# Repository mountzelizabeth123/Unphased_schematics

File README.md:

# UnPhased KiCad Project Repository

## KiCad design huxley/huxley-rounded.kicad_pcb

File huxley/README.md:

Board: Huxley
# Layers: 4
Board Dimensions: 4.88in x 4.88in (124mm x 124mm)
Min Size Hole: 0.01in
# Holes: 528
Assembly Both Sides: Y
Standard Chip IO: N
Blink Vias: N
Via in pads: Y

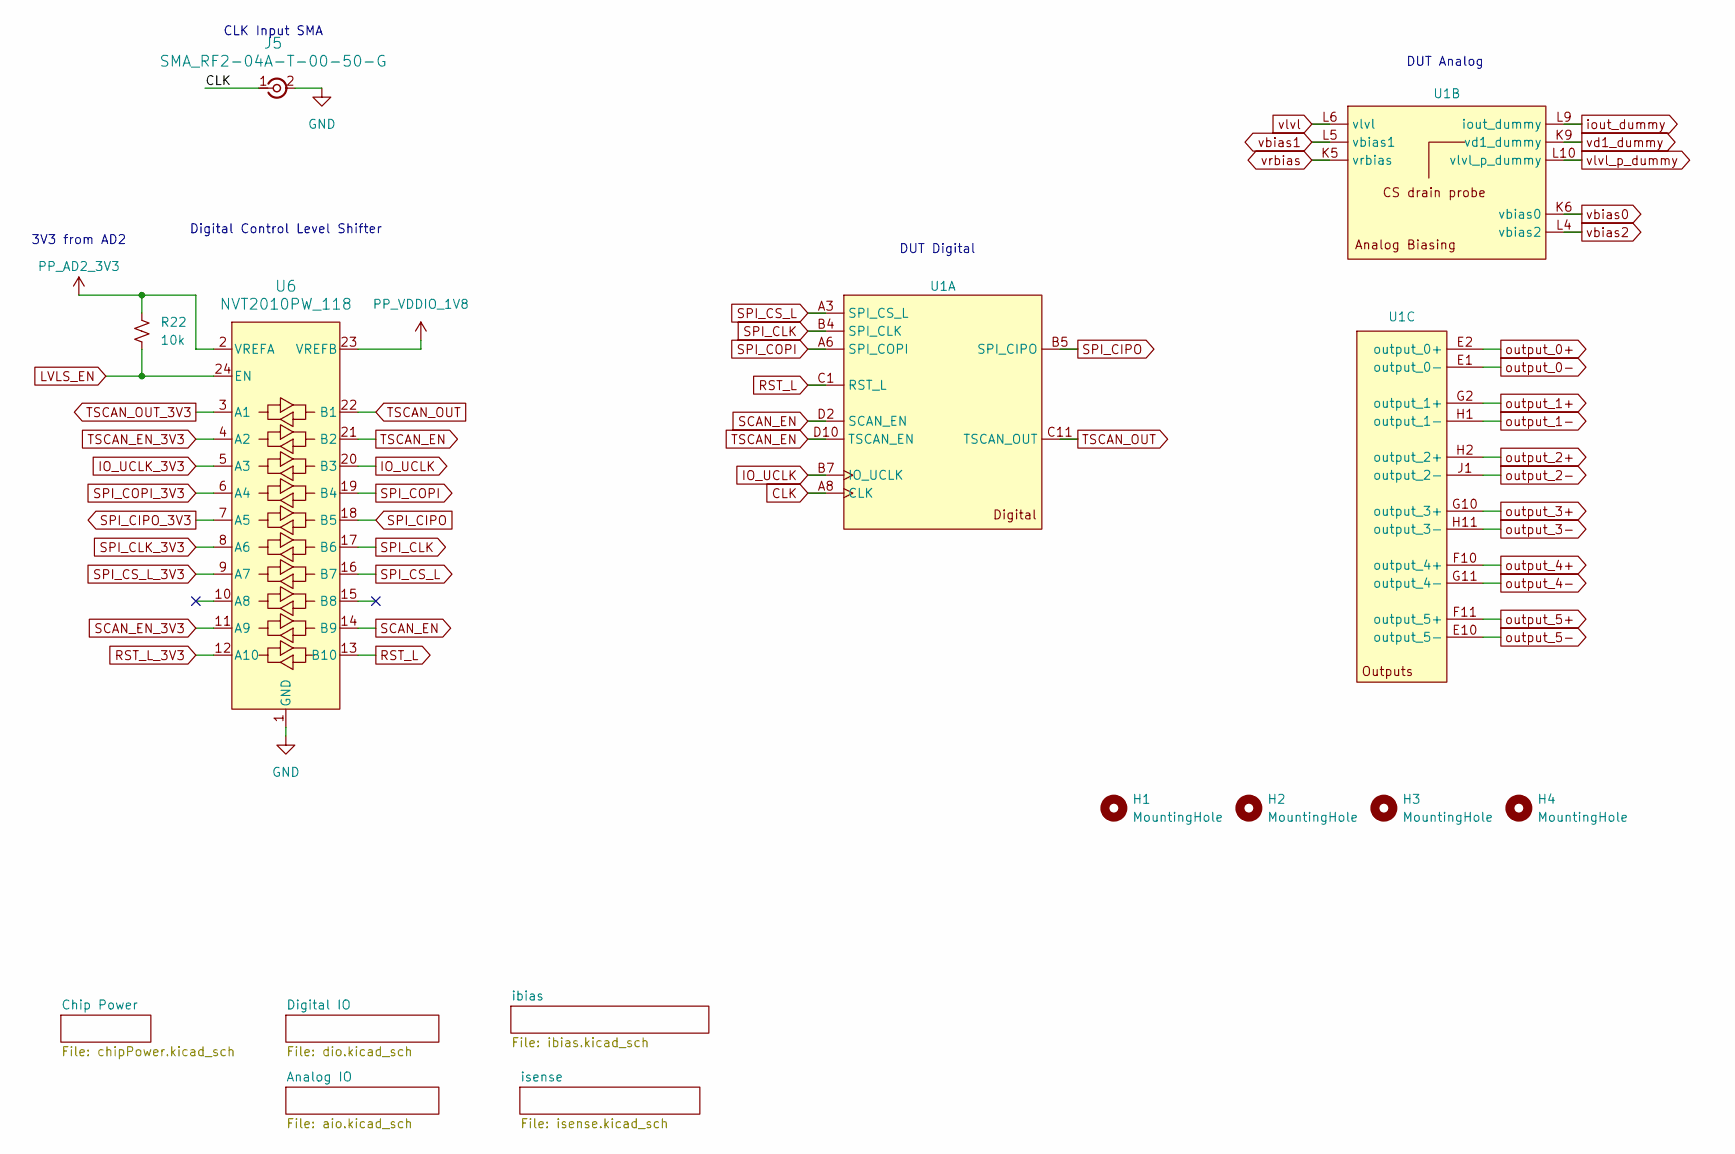
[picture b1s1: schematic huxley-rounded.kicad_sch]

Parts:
H1, H2, H3, H4: MountingHole; MountingHole_3.2mm_M3_DIN965_Pad_TopBottom
J5: SMA_RF2-04A-T-00-50-G; CONN_RF2-04A-T-00-50-G_ADM
R22: 10k; R_0603_1608Metric
U1: CPG08462_Full
U6: NVT2010PW_118; TSSOP24_SOT355-1_NXP

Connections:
CLK: J5.1, U1.A8 (CLK); also elsewhere on the board
GND: J5.2, J5.3 (Ext), J5.4 (Ext), J5.5 (Ext), U6.1 (GND); also elsewhere on the board
IO_UCLK: U1.B7 (IO_UCLK), U6.20 (B3)
IO_UCLK_3V3: U6.5 (A3); also elsewhere on the board
LVLS_EN: R22.2, U6.24 (EN); also elsewhere on the board
PP_AD2_3V3: R22.1, U6.2 (VREFA); also elsewhere on the board
PP_VDDIO_1V8: U6.23 (VREFB); also elsewhere on the board
RST_L: U1.C1 (RST_L), U6.13 (B10)
RST_L_3V3: U6.12 (A10); also elsewhere on the board
SCAN_EN: U1.D2 (SCAN_EN), U6.14 (B9)
SCAN_EN_3V3: U6.11 (A9); also elsewhere on the board
SPI_CIPO: U1.B5 (SPI_CIPO), U6.18 (B5)
SPI_CIPO_3V3: U6.7 (A5); also elsewhere on the board
SPI_CLK: U1.B4 (SPI_CLK), U6.17 (B6)
SPI_CLK_3V3: U6.8 (A6); also elsewhere on the board
SPI_COPI: U1.A6 (SPI_COPI), U6.19 (B4)
SPI_COPI_3V3: U6.6 (A4); also elsewhere on the board
SPI_CS_L: U1.A3 (SPI_CS_L), U6.16 (B7)
SPI_CS_L_3V3: U6.9 (A7); also elsewhere on the board
TSCAN_EN: U1.D10 (TSCAN_EN), U6.21 (B2)
TSCAN_EN_3V3: U6.4 (A2); also elsewhere on the board
TSCAN_OUT: U1.C11 (TSCAN_OUT), U6.22 (B1)
TSCAN_OUT_3V3: U6.3 (A1); also elsewhere on the board
iout_dummy: U1.L9 (iout_dummy); also elsewhere on the board
output_0+: U1.E2 (output_0+); also elsewhere on the board
output_0-: U1.E1 (output_0-); also elsewhere on the board
output_1+: U1.G2 (output_1+); also elsewhere on the board
output_1-: U1.H1 (output_1-); also elsewhere on the board
output_2+: U1.H2 (output_2+); also elsewhere on the board
output_2-: U1.J1 (output_2-); also elsewhere on the board
output_3+: U1.G10 (output_3+); also elsewhere on the board
output_3-: U1.H11 (output_3-); also elsewhere on the board
output_4+: U1.F10 (output_4+); also elsewhere on the board
output_4-: U1.G11 (output_4-); also elsewhere on the board
output_5+: U1.F11 (output_5+); also elsewhere on the board
output_5-: U1.E10 (output_5-); also elsewhere on the board
vbias0: U1.K6 (vbias0); also elsewhere on the board
vbias1: U1.L5 (vbias1); also elsewhere on the board
vbias2: U1.L4 (vbias2); also elsewhere on the board
vd1_dummy: U1.K9 (vd1_dummy); also elsewhere on the board
vlvl: U1.L6 (vlvl); also elsewhere on the board
vlvl_p_dummy: U1.L10 (vlvl_p_dummy); also elsewhere on the board
vrbias: U1.K5 (vrbias); also elsewhere on the board

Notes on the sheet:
DUT Digital
DUT Analog
CLK Input SMA
3V3 from AD2
Digital Control Level Shifter

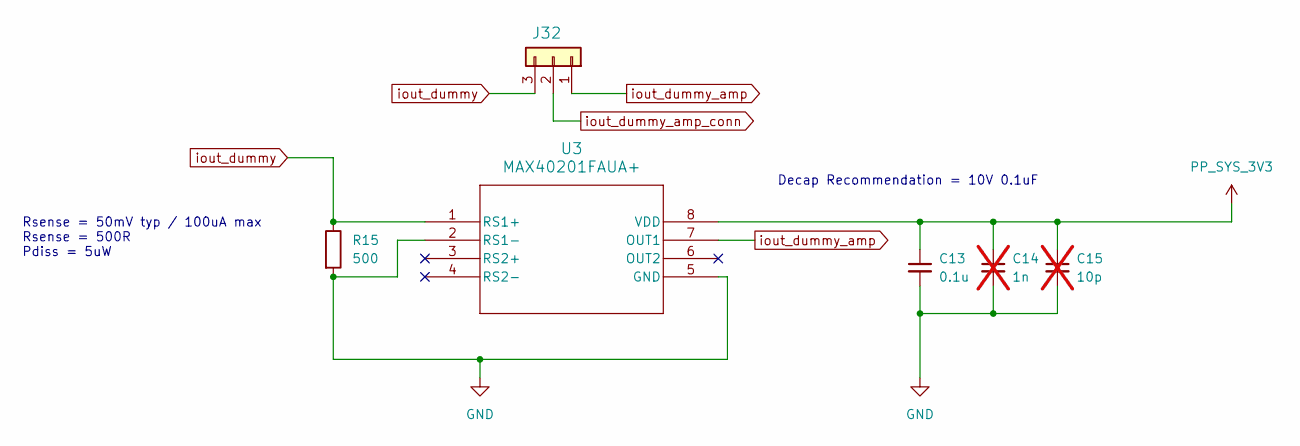
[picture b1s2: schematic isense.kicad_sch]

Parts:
C13: 0.1u; C_0603_1608Metric
C14: 1n; C_0603_1608Metric; not fitted
C15: 10p; C_0603_1608Metric; not fitted
J32: 61300211121; PinHeader_1x03_P2.54mm_Vertical
R15: 500; R_0603_1608Metric
U3: MAX40201FAUA+

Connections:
GND: C13.2, C14.2, C15.2, R15.2, U3.2 (RS1-), U3.5 (GND); also elsewhere on the board
PP_SYS_3V3: C13.1, C14.1, C15.1, U3.8 (VDD); also elsewhere on the board
iout_dummy: J32.3, R15.1, U3.1 (RS1+); also elsewhere on the board
iout_dummy_amp: J32.1, U3.7 (OUT1)
iout_dummy_amp_conn: J32.2; also elsewhere on the board

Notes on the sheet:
Decap Recommendation = 10V 0.1uF
Rsense = 50mV typ / 100uA max Rsense = 500R Pdiss = 5uW

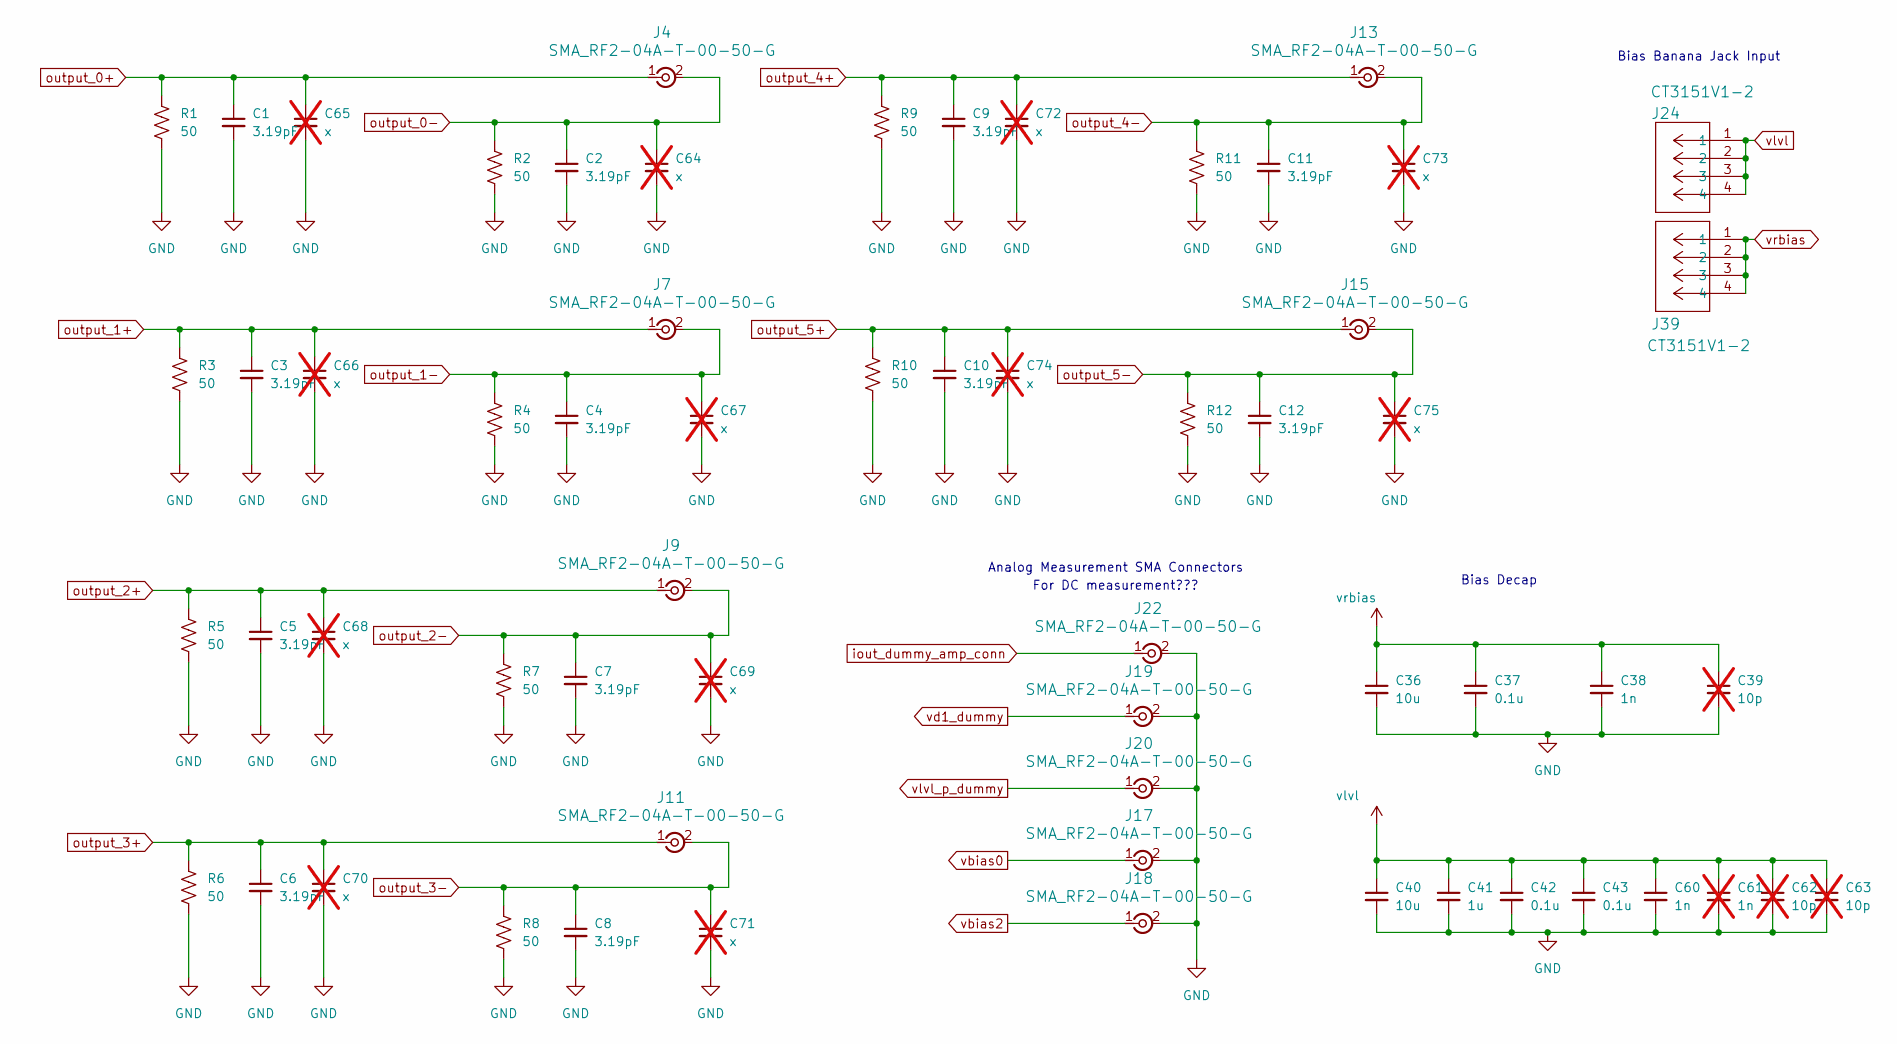
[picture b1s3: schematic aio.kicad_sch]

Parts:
C1, C2, C3, C4, C5, C6, C7, C8, C9, C10, C11, C12: 3.19pF; C_0603_1608Metric
C36, C40: 10u; C_0603_1608Metric
C37, C42, C43: 0.1u; C_0603_1608Metric
C38, C60: 1n; C_0603_1608Metric
C39, C62, C63: 10p; C_0603_1608Metric; not fitted
C41: 1u; C_0603_1608Metric
C61: 1n; C_0603_1608Metric; not fitted
C64, C65, C66, C67, C68, C69, C70, C71, C72, C73, C74, C75: x; C_0603_1608Metric; not fitted
J4, J7, J9, J11, J13, J15, J17, J18, J19, J20, J22: SMA_RF2-04A-T-00-50-G; CONN_RF2-04A-T-00-50-G_ADM
J24, J39: CT3151V1-2; banana_plug_CT3151V1-0
R1, R2, R3, R4, R5, R6, R7, R8, R9, R10, R11, R12: 50; R_0603_1608Metric_Vishay_WBT

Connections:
GND: C1.2, C2.2, C3.2, C4.2, C5.2, C6.2, C7.2, C8.2, C9.2, C10.2, C11.2, C12.2, C36.2, C37.2, C38.2, C39.2, C40.2, C41.2, C42.2, C43.2, C60.2, C61.2, C62.2, C63.2, C64.2, C65.2, C66.2, C67.2, C68.2, C69.2, C70.2, C71.2, C72.2, C73.2, C74.2, C75.2, J17.2, J17.3 (Ext), J17.4 (Ext), J17.5 (Ext), J18.2, J18.3 (Ext), J18.4 (Ext), J18.5 (Ext), J19.2, J19.3 (Ext), J19.4 (Ext), J19.5 (Ext), J20.2, J20.3 (Ext), J20.4 (Ext), J20.5 (Ext), J22.2, J22.3 (Ext), J22.4 (Ext), J22.5 (Ext), R1.2, R2.2, R3.2, R4.2, R5.2, R6.2, R7.2, R8.2, R9.2, R10.2, R11.2, R12.2; also elsewhere on the board
iout_dummy_amp_conn: J22.1; also elsewhere on the board
output_0+: C1.1, C65.1, J4.1, R1.1; also elsewhere on the board
output_0-: C2.1, C64.1, J4.2, J4.3 (Ext), J4.4 (Ext), J4.5 (Ext), R2.1; also elsewhere on the board
output_1+: C3.1, C66.1, J7.1, R3.1; also elsewhere on the board
output_1-: C4.1, C67.1, J7.2, J7.3 (Ext), J7.4 (Ext), J7.5 (Ext), R4.1; also elsewhere on the board
output_2+: C5.1, C68.1, J9.1, R5.1; also elsewhere on the board
output_2-: C7.1, C69.1, J9.2, J9.3 (Ext), J9.4 (Ext), J9.5 (Ext), R7.1; also elsewhere on the board
output_3+: C6.1, C70.1, J11.1, R6.1; also elsewhere on the board
output_3-: C8.1, C71.1, J11.2, J11.3 (Ext), J11.4 (Ext), J11.5 (Ext), R8.1; also elsewhere on the board
output_4+: C9.1, C72.1, J13.1, R9.1; also elsewhere on the board
output_4-: C11.1, C73.1, J13.2, J13.3 (Ext), J13.4 (Ext), J13.5 (Ext), R11.1; also elsewhere on the board
output_5+: C10.1, C74.1, J15.1, R10.1; also elsewhere on the board
output_5-: C12.1, C75.1, J15.2, J15.3 (Ext), J15.4 (Ext), J15.5 (Ext), R12.1; also elsewhere on the board
vbias0: J17.1; also elsewhere on the board
vbias2: J18.1; also elsewhere on the board
vd1_dummy: J19.1; also elsewhere on the board
vlvl: C40.1, C41.1, C42.1, C43.1, C60.1, C61.1, C62.1, C63.1, J24.1, J24.2, J24.3, J24.4; also elsewhere on the board
vlvl_p_dummy: J20.1; also elsewhere on the board
vrbias: C36.1, C37.1, C38.1, C39.1, J39.1, J39.2, J39.3, J39.4; also elsewhere on the board

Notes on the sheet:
Analog Measurement SMA Connectors
Bias Decap
Bias Banana Jack Input
For DC measurement???

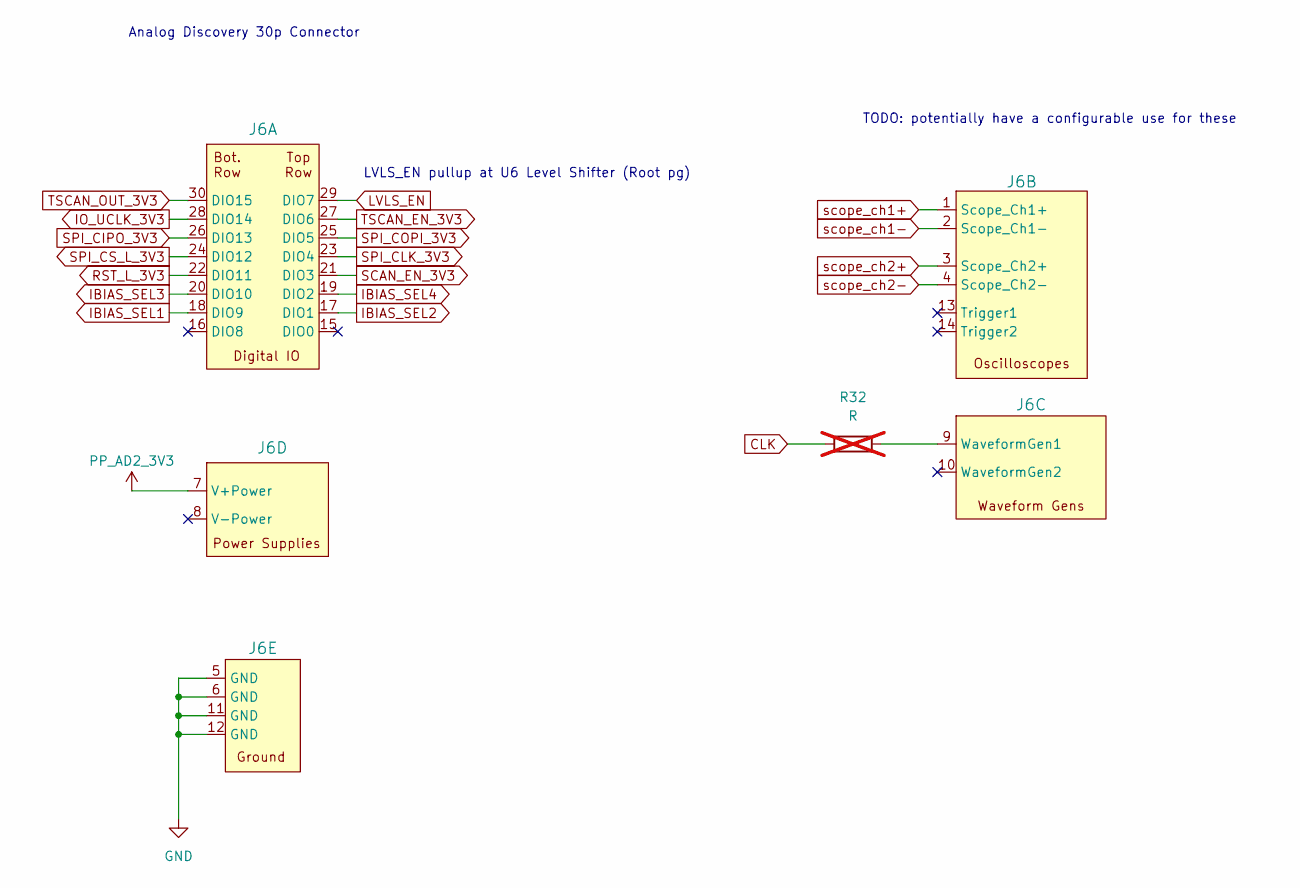
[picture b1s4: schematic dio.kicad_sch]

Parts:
J6: PinHeader_2x15_P2.54mm_Horizontal
R32: R; R_0603_1608Metric; not fitted

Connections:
CLK: R32.1; also elsewhere on the board
GND: J6.5 (GND), J6.6 (GND), J6.11 (GND), J6.12 (GND); also elsewhere on the board
IBIAS_SEL1: J6.18 (DIO9); also elsewhere on the board
IBIAS_SEL2: J6.17 (DIO1); also elsewhere on the board
IBIAS_SEL3: J6.20 (DIO10); also elsewhere on the board
IBIAS_SEL4: J6.19 (DIO2); also elsewhere on the board
IO_UCLK_3V3: J6.28 (DIO14); also elsewhere on the board
LVLS_EN: J6.29 (DIO7); also elsewhere on the board
unnamed: J6.9 (WaveformGen1), R32.2
PP_AD2_3V3: J6.7 (V+Power); also elsewhere on the board
RST_L_3V3: J6.22 (DIO11); also elsewhere on the board
SCAN_EN_3V3: J6.21 (DIO3); also elsewhere on the board
SPI_CIPO_3V3: J6.26 (DIO13); also elsewhere on the board
SPI_CLK_3V3: J6.23 (DIO4); also elsewhere on the board
SPI_COPI_3V3: J6.25 (DIO5); also elsewhere on the board
SPI_CS_L_3V3: J6.24 (DIO12); also elsewhere on the board
TSCAN_EN_3V3: J6.27 (DIO6); also elsewhere on the board
TSCAN_OUT_3V3: J6.30 (DIO15); also elsewhere on the board
scope_ch1+: J6.1 (Scope_Ch1+)
scope_ch1-: J6.2 (Scope_Ch1-)
scope_ch2+: J6.3 (Scope_Ch2+)
scope_ch2-: J6.4 (Scope_Ch2-)

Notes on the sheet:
Analog Discovery 30p Connector
LVLS_EN pullup at U6 Level Shifter (Root pg)
TODO: potentially have a configurable use for these

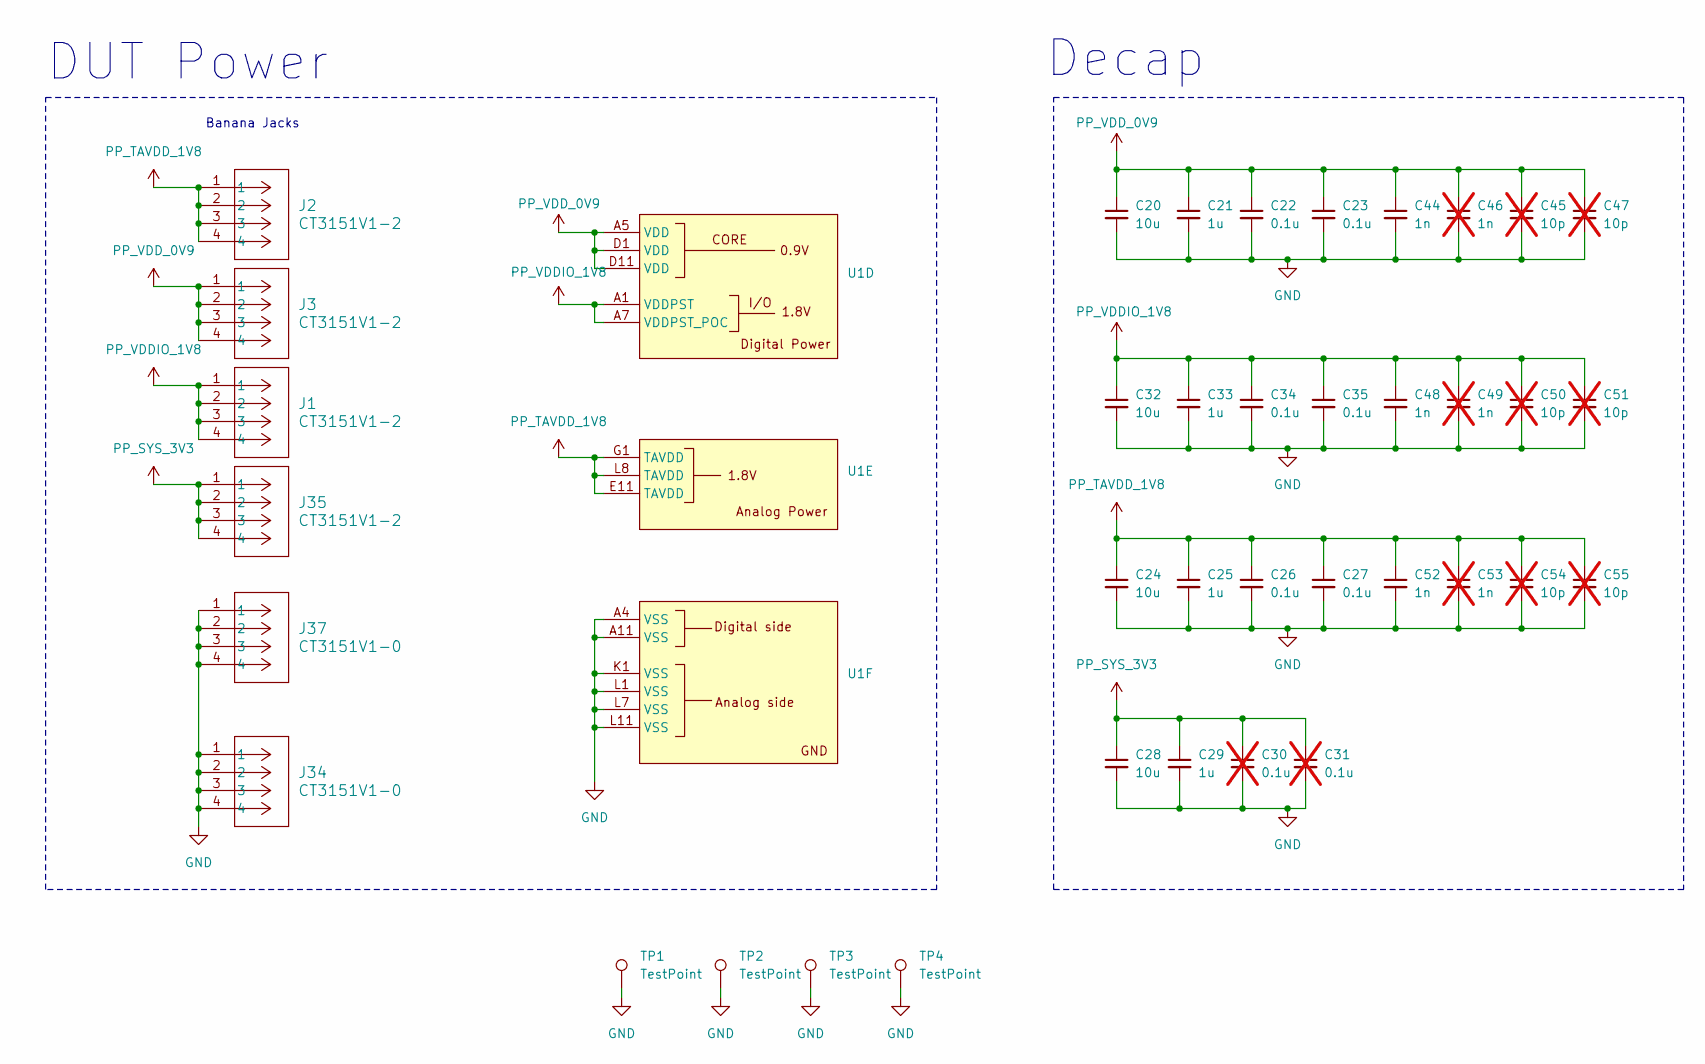
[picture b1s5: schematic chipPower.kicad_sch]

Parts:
C20, C24, C28, C32: 10u; C_0603_1608Metric
C21, C25, C29, C33: 1u; C_0603_1608Metric
C22, C23, C26, C27, C34, C35: 0.1u; C_0603_1608Metric
C30, C31: 0.1u; C_0603_1608Metric; not fitted
C44, C48, C52: 1n; C_0603_1608Metric
C45, C47, C50, C51, C54, C55: 10p; C_0603_1608Metric; not fitted
C46, C49, C53: 1n; C_0603_1608Metric; not fitted
J1, J2, J3, J35: CT3151V1-2; banana_plug_CT3151V1-0
J34, J37: CT3151V1-0; banana_plug_CT3151V1-0
TP1, TP2, TP3, TP4: TestPoint; TestPoint_Pad_D3.0mm
U1: CPG08462_Full

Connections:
GND: C20.2, C21.2, C22.2, C23.2, C24.2, C25.2, C26.2, C27.2, C28.2, C29.2, C30.2, C31.2, C32.2, C33.2, C34.2, C35.2, C44.2, C45.2, C46.2, C47.2, C48.2, C49.2, C50.2, C51.2, C52.2, C53.2, C54.2, C55.2, J34.1, J34.2, J34.3, J34.4, J37.1, J37.2, J37.3, J37.4, TP1.1, TP2.1, TP3.1, TP4.1, U1.A4 (VSS), U1.A11 (VSS), U1.K1 (VSS), U1.L1 (VSS), U1.L7 (VSS), U1.L11 (VSS); also elsewhere on the board
PP_SYS_3V3: C28.1, C29.1, C30.1, C31.1, J35.1, J35.2, J35.3, J35.4; also elsewhere on the board
PP_TAVDD_1V8: C24.1, C25.1, C26.1, C27.1, C52.1, C53.1, C54.1, C55.1, J2.1, J2.2, J2.3, J2.4, U1.E11 (TAVDD), U1.G1 (TAVDD), U1.L8 (TAVDD)
PP_VDDIO_1V8: C32.1, C33.1, C34.1, C35.1, C48.1, C49.1, C50.1, C51.1, J1.1, J1.2, J1.3, J1.4, U1.A1 (VDDPST), U1.A7 (VDDPST_POC); also elsewhere on the board
PP_VDD_0V9: C20.1, C21.1, C22.1, C23.1, C44.1, C45.1, C46.1, C47.1, J3.1, J3.2, J3.3, J3.4, U1.A5 (VDD), U1.D1 (VDD), U1.D11 (VDD)

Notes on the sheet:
Decap
DUT Power
Banana Jacks

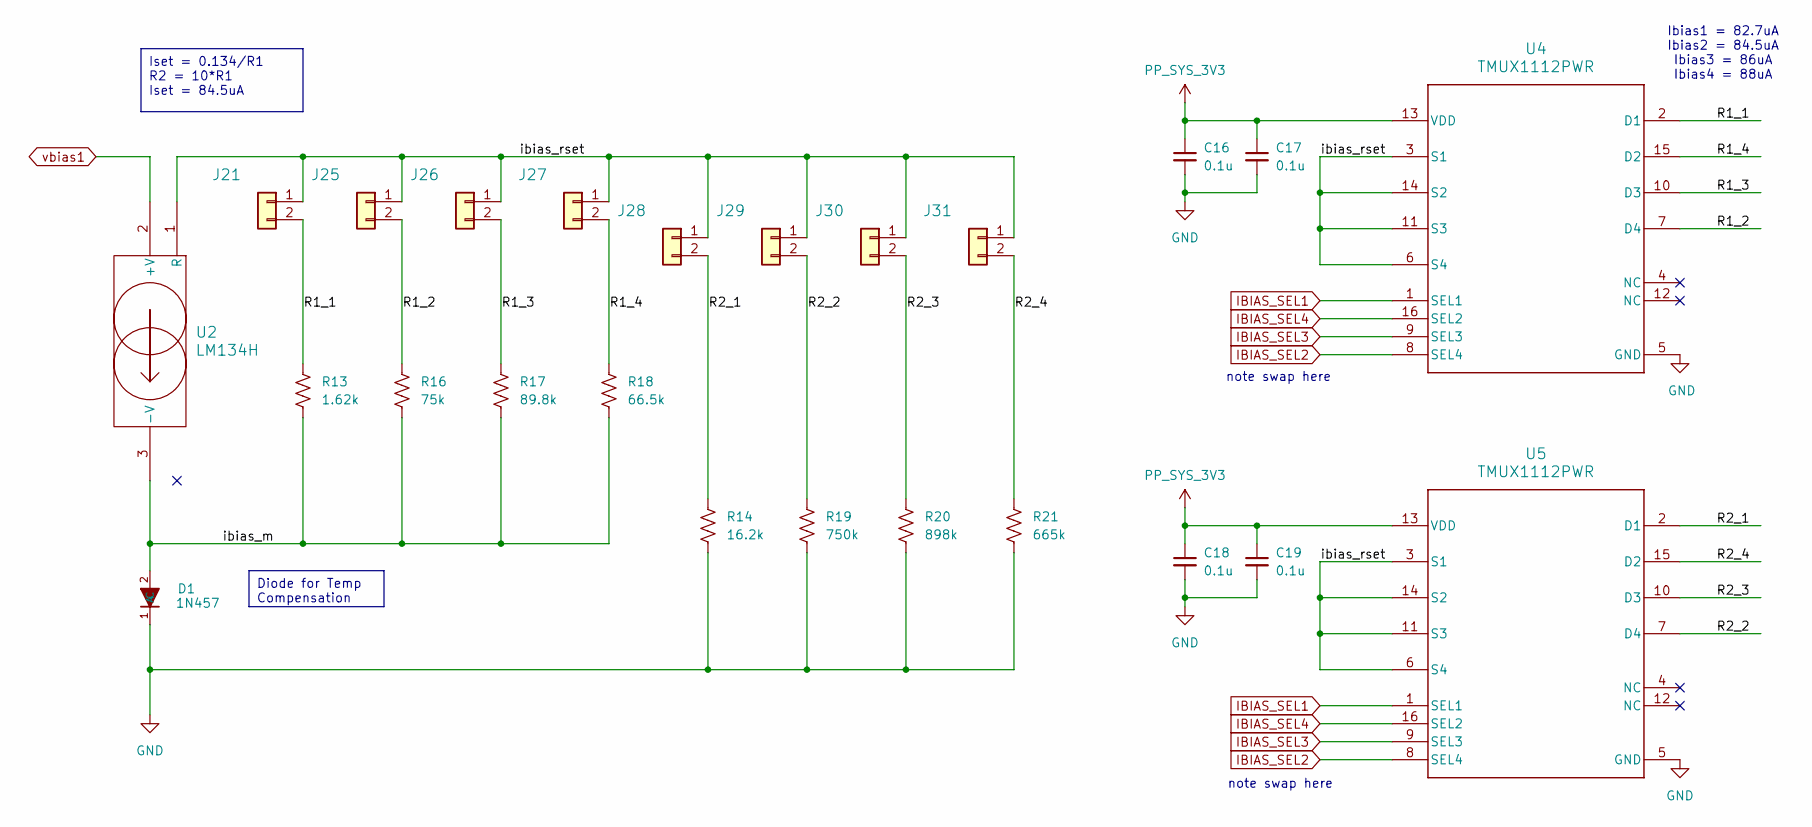
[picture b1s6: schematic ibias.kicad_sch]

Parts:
C16, C17, C18, C19: 0.1u; C_0603_1608Metric
D1: 1N457; DIO_1N457; MPN 1N457
J21, J25, J26, J27, J28, J29, J30, J31: 61300211121; PinHeader_1x02_P2.54mm_Vertical
R13: 1.62k; R_0603_1608Metric
R14: 16.2k; R_0603_1608Metric
R16: 75k; R_0603_1608Metric
R17: 89.8k; R_0603_1608Metric
R18: 66.5k; R_0603_1608Metric
R19: 750k; R_0603_1608Metric
R20: 898k; R_0603_1608Metric
R21: 665k; R_0603_1608Metric
U2: LM134H; TO-46-3
U4, U5: TMUX1112PWR; TSSOP-16_4.4x5mm_P0.65mm

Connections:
/ibias/R1_1: J21.2, R13.1, U4.2 (D1)
/ibias/R1_2: J25.2, R16.1, U4.7 (D4)
/ibias/R1_3: J26.2, R17.1, U4.10 (D3)
/ibias/R1_4: J27.2, R18.1, U4.15 (D2)
/ibias/R2_1: J28.2, R14.1, U5.2 (D1)
/ibias/R2_2: J29.2, R19.1, U5.7 (D4)
/ibias/R2_3: J30.2, R20.1, U5.10 (D3)
/ibias/R2_4: J31.2, R21.1, U5.15 (D2)
/ibias/ibias_m: D1.2 (A), R13.2, R16.2, R17.2, R18.2, U2.3 (-V)
/ibias/ibias_rset: J21.1, J25.1, J26.1, J27.1, J28.1, J29.1, J30.1, J31.1, U2.1 (R), U4.3 (S1), U4.6 (S4), U4.11 (S3), U4.14 (S2), U5.3 (S1), U5.6 (S4), U5.11 (S3), U5.14 (S2)
GND: C16.2, C17.2, C18.2, C19.2, D1.1 (C), R14.2, R19.2, R20.2, R21.2, U4.5 (GND), U5.5 (GND); also elsewhere on the board
IBIAS_SEL1: U4.1 (SEL1), U5.1 (SEL1); also elsewhere on the board
IBIAS_SEL2: U4.8 (SEL4), U5.8 (SEL4); also elsewhere on the board
IBIAS_SEL3: U4.9 (SEL3), U5.9 (SEL3); also elsewhere on the board
IBIAS_SEL4: U4.16 (SEL2), U5.16 (SEL2); also elsewhere on the board
PP_SYS_3V3: C16.1, C17.1, C18.1, C19.1, U4.13 (VDD), U5.13 (VDD); also elsewhere on the board
vbias1: U2.2 (+V); also elsewhere on the board

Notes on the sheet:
Iset = 0.134/R1 R2 = 10*R1 Iset = 84.5uA
Diode for Temp Compensation
Ibias1 = 82.7uA Ibias2 = 84.5uA Ibias3 = 86uA Ibias4 = 88uA
note swap here

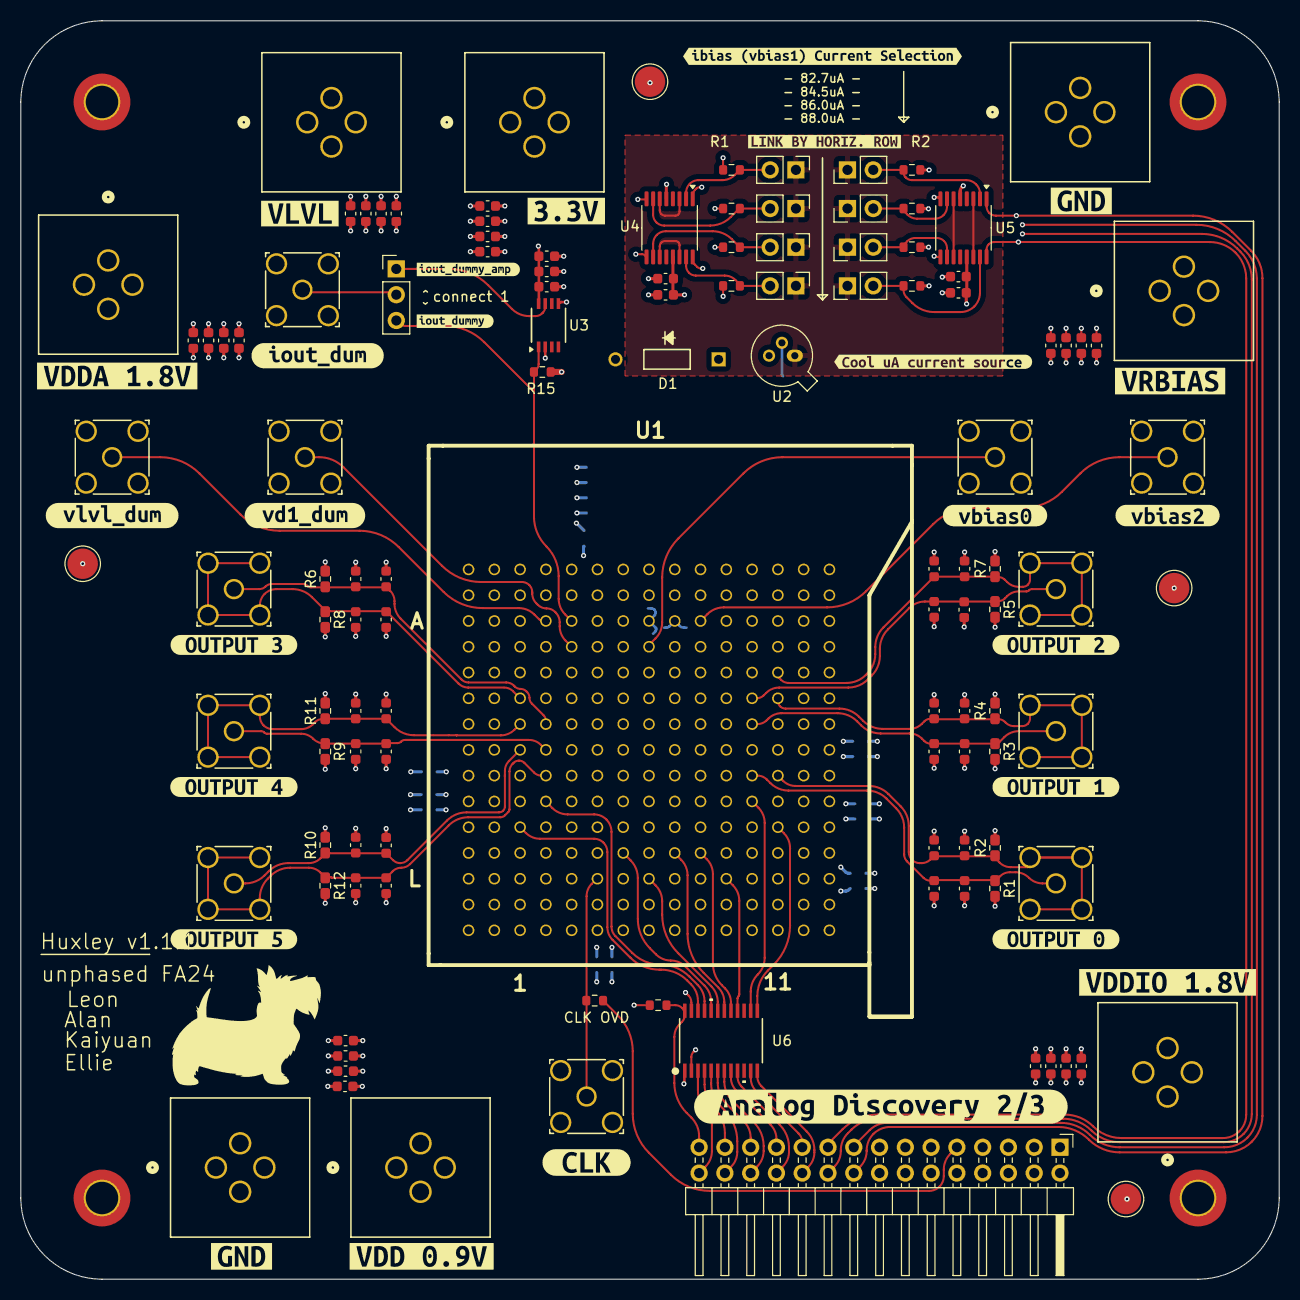
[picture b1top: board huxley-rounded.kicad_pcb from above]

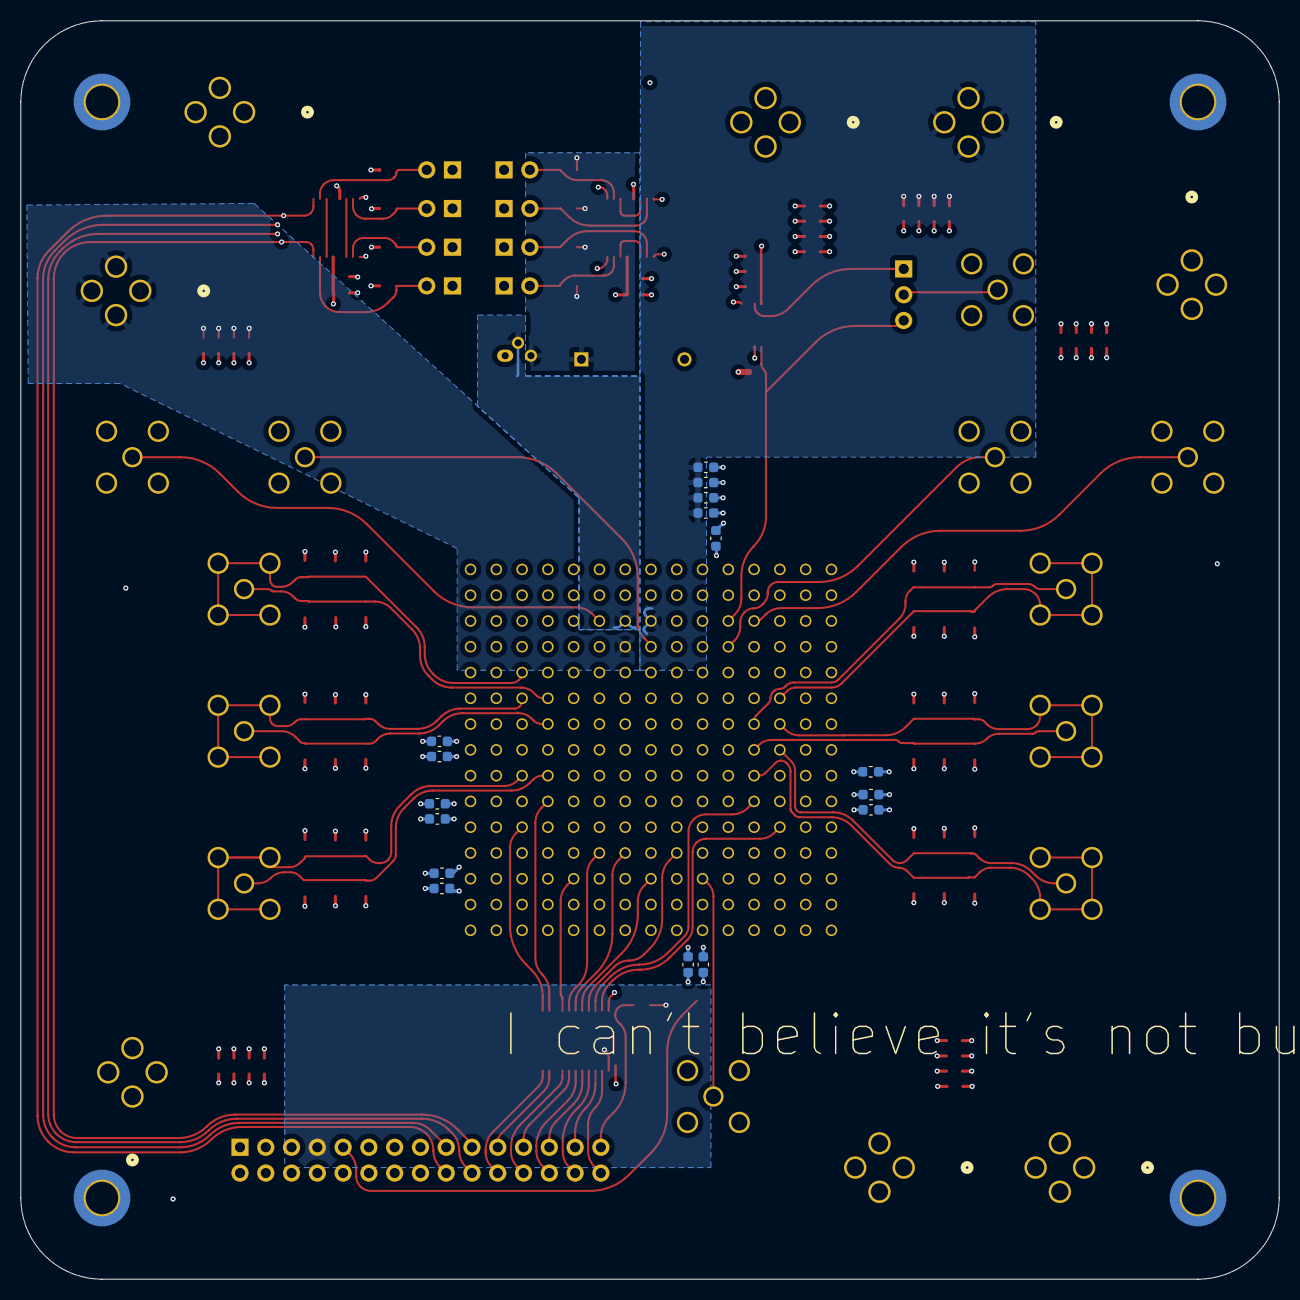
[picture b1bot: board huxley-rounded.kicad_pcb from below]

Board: 4 copper layers, 124.0 x 124.0 mm, 165 parts (16 on the bottom side), 63 nets.

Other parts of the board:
kibuzzard-6717DA4B: G***; kibuzzard-6717DA4B
kibuzzard-6717DA65: G***; kibuzzard-6717DA65
kibuzzard-6717E4EA: G***; kibuzzard-6717E4EA
kibuzzard-6717E6BD: G***; kibuzzard-6717E6BD
kibuzzard-6717E6C2: G***; kibuzzard-6717E6C2
kibuzzard-6717E6C7: G***; kibuzzard-6717E6C7
kibuzzard-6717E514: G***; kibuzzard-6717E514
kibuzzard-6717E567: G***; kibuzzard-6717E567
kibuzzard-6717E572: G***; kibuzzard-6717E572
kibuzzard-6717E585: G***; kibuzzard-6717E585
kibuzzard-6717ED1A, kibuzzard-6717ED1A#2: G***; kibuzzard-6717ED1A
kibuzzard-6717ED7A: G***; kibuzzard-6717ED7A
kibuzzard-6717ED42: G***; kibuzzard-6717ED42
kibuzzard-6717ED63: G***; kibuzzard-6717ED63
kibuzzard-6717ED92: G***; kibuzzard-6717ED92
kibuzzard-6717EDA4: G***; kibuzzard-6717EDA4
kibuzzard-6717EDC6: G***; kibuzzard-6717EDC6
kibuzzard-6717EEBB: G***; kibuzzard-6717EEBB
kibuzzard-6717EECA: G***; kibuzzard-6717EECA
kibuzzard-6717EEDA: G***; kibuzzard-6717EEDA
kibuzzard-6717EF01: G***; kibuzzard-6717EF01
kibuzzard-6717EF05: G***; kibuzzard-6717EF05
kibuzzard-6717EF67: G***; kibuzzard-6717EF67
kibuzzard-6717F3BE: G***; kibuzzard-6717F3BE
kibuzzard-6717F38C: G***; kibuzzard-6717F38C

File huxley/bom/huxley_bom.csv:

Reference,Value,Datasheet,Footprint,Qty,DNP,Manufactuer Part Number,Supplier,Supplier Part Number
"C1,C2,C3,C4,C5,C6,C7,C8,C9,C10,C11,C12",3.19pF,~,Capacitor_SMD:C_0603_1608Metric,12,,CBR06C329B5GACAUTO,Digikey,399-CBR06C329B5GACAUTOCT-ND
"C13,C16,C17,C18,C19,C22,C23,C26,C27,C34,C35,C37,C42,C43,C30,C31",0.1u,~,Capacitor_SMD:C_0603_1608Metric,14,,CC0603KRX7R7BB104,Digikey,311-1088-1-ND
"C14,C46,C49,C53,C61,C38,C44,C48,C52,C60",1n,~,Capacitor_SMD:C_0603_1608Metric,5,DNP,GCM188R71H102KA37D,Digikey,490-4777-1-ND
"C15,C39,C45,C47,C50,C51,C54,C55,C62,C63",10p,~,Capacitor_SMD:C_0603_1608Metric,10,DNP,GCM1885C1H100JA16D,Digikey,490-4766-1-ND
"C20,C24,C28,C32,C36,C40",10u,~,Capacitor_SMD:C_0603_1608Metric,6,,CL10A106MQ8NNNC,Digikey,1276-1119-1-ND
"C21,C25,C29,C33,C41",1u,~,Capacitor_SMD:C_0603_1608Metric,5,,CL10B105KP8NNNC,Digikey,1276-1946-1-ND
"C64,C65,C66,C67,C68,C69,C70,C71,C72,C73,C74,C75",x,~,Capacitor_SMD:C_0603_1608Metric,12,DNP,,Digikey,
D1,1N457,,0_726_footprints:DIO_1N457,1,,1N457,Digikey,1N457FS-ND
"J1,J2,J3,J24,J35,J39",CT3151V1-2,CT3151V1-0,0_726_footprints:banana_plug_CT3151V1-0,6,,CT3151V1-2,Digikey,CT3151V1-2-ND
"J4,J5,J7,J9,J11,J13,J15,J17,J18,J19,J20,J22",SMA_RF2-04A-T-00-50-G,112404,0_726_footprints:CONN_RF2-04A-T-00-50-G_ADM,12,,RF2-04A-T-00-50-G,Digikey,2057-RF2-04A-T-00-50-G-ND
J6,~,https://digilent.com/reference/test-and-measurement/analog-d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,Connector_PinHeader_2.54mm:PinHeader_2x15_P2.54mm_Horizontal,1,,67996-130HLF,Digikey,609-3456-ND
"J21,J25,J26,J27,J28,J29,J30,J31",61300211121,~,Connector_PinHeader_2.54mm:PinHeader_1x02_P2.54mm_Vertical,8,,61300211121,Digikey,732-5315-ND
J32,61300211121,~,Connector_PinHeader_2.54mm:PinHeader_1x03_P2.54mm_Vertical,1,,61300311121,Digikey,732-5316-ND
"J34,J37",CT3151V1-0,CT3151V1-0,0_726_footprints:banana_plug_CT3151V1-0,2,,CT3151V1-0,Digikey,CT3151V1-0-ND
"R1,R2,R3,R4,R5,R6,R7,R8,R9,R10,R11,R12",50,~,Resistor_SMD:R_0603_1608Metric,12,,RCP0603W50R0GEB,Digikey,541-2655-1-ND
R13,1.62k,~,Resistor_SMD:R_0603_1608Metric,1,,RC0603FR-071K62L,Digikey,311-1.62KHRCT-ND
R14,16.2k,~,Resistor_SMD:R_0603_1608Metric,1,,RC0603FR-0716K2L,Digikey,311-16.2KHRCT-ND
R15,500,~,Resistor_SMD:R_0603_1608Metric,1,,RT0603BRC07500RL,Digikey,13-RT0603BRC07500RLCT-ND
R16,75k,~,Resistor_SMD:R_0603_1608Metric,1,,AC0603FR-0775KL,Digikey,YAG3629CT-ND
R17,89.8k,~,Resistor_SMD:R_0603_1608Metric,1,,PATT0603E8982BGT1,Digikey,764-1031-1-ND
R18,66.5k,~,Resistor_SMD:R_0603_1608Metric,1,,AC0603FR-0766K5L,Digikey,YAG3623CT-ND
R19,750k,~,Resistor_SMD:R_0603_1608Metric,1,,RMCF0603FT750K,Digikey,RMCF0603FT750KCT-ND
R20,898k,~,Resistor_SMD:R_0603_1608Metric,1,,RN73H1JTTD8983D50,Digikey,2019-RN73H1JTTD8983D50CT-ND
R21,665k,~,Resistor_SMD:R_0603_1608Metric,1,,RC0603FR-07665KL,Digikey,311-665KHRCT-ND
R22,10k,~,Resistor_SMD:R_0603_1608Metric,1,,RMCF0603JT10K0CT-ND,Digikey,RMCF0603JT10K0
U1,~,,-- mixed values --,1,,,Digikey,
U2,LM134H,LM134H,Package_TO_SOT_THT:TO-46-3,1,,LM134H,Digikey,296-38977-ND
U3,MAX40201FAUA+,MAX40201FAUA+,0_726_footprints:MAX40201FAUA+,1,,MAX40201FAUA+,Digikey,MAX40201FAUA+-ND
"U4,U5",TMUX1112PWR,TMUX1111PWR,Package_SO:TSSOP-16_4.4x5mm_P0.65mm,2,,TMUX1112PWR,Digikey,296-TMUX1111PWRCT-ND
U6,NVT2010PW_118,NVT2010PW_118,0_726_footprints:TSSOP24_SOT355-1_NXP,1,,"NVT2010PW,118",Digikey,568-5299-1-ND
